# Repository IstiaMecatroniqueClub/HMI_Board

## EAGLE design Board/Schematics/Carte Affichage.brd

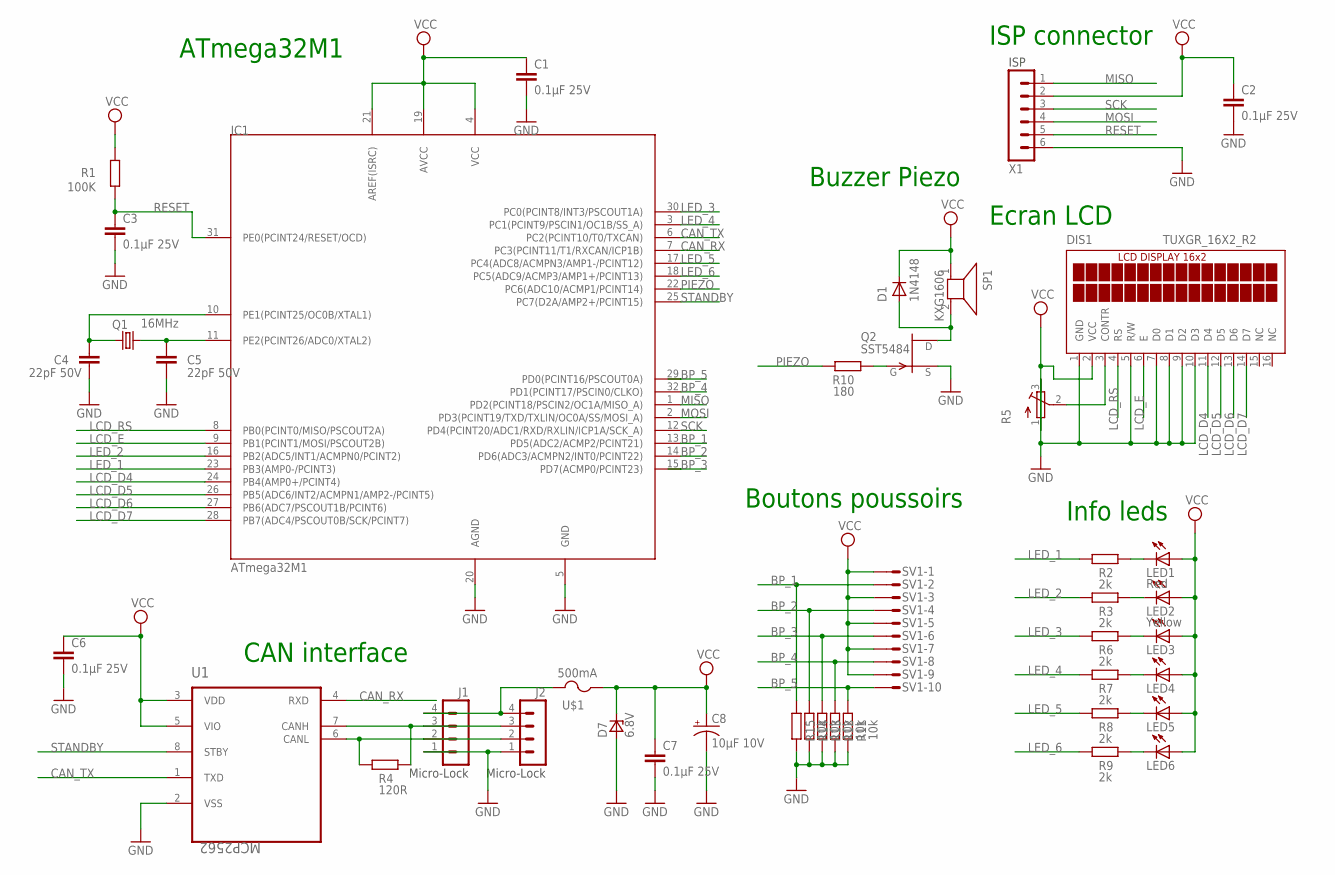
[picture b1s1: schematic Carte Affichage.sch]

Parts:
C1, C2, C3, C6, C7: 0.1µF 25V; C2012
C4, C5: 22pF 50V; C2012
C8: 10µF 10V; EIA3216
D1: 1N4148; SMA-DO214AC
D7: 6.8V; DO-214AA
DIS1: TUXGR_16X2_R2
IC1: ATmega32M1; TQFP32
J1, J2: Micro-Lock; 504195-0470
LED1: Red; VLD
LED2: Yellow; VLD
LED3, LED4, LED5, LED6: LED5MM
Q1: 16MHz; SMD_KX7
Q2: SST5484; SOT23
R1: 100K; R2012
R2, R3, R6, R7, R8, R9: 2k; R2012
R4: 120R; R2012
R5: R-TRIMM3299W; RTRIM3299W
R10: 180; R2012
R11, R12, R13, R14, R15: 10k; R2012
SP1: KXG1606; AL23P
SV1: S10P; S10P2
U1: MCP2562; SOIC8
U$1: 500mA; EIARS-481-2
X1: ISP; MINITEK_127_6WAY_SMD

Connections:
BP_1: IC1.13 (PD5(ADC2/ACMP2/PCINT21)), R15.2, SV1.P$2
BP_2: IC1.14 (PD6(ADC3/ACMPN2/INT0/PCINT22)), R14.2, SV1.P$4
BP_3: IC1.15 (PD7(ACMP0/PCINT23)), R13.2, SV1.P$6
BP_4: IC1.32 (PD1(PCINT17/PSCIN0/CLKO)), R12.2, SV1.P$8
BP_5: IC1.29 (PD0(PCINT16/PSCOUT0A)), R11.2, SV1.P$10
CAN_RX: IC1.7 (PC3(PCINT11/T1/RXCAN/ICP1B)), U1.4 (RXD)
CAN_TX: IC1.6 (PC2(PCINT10/T0/TXCAN)), U1.1 (TXD)
GND: C1.2, C2.2, C3.2, C4.2, C5.2, C6.2, C7.2, C8.C (-), D7.A, DIS1.1 (GND), DIS1.5 (R/W), DIS1.7 (D0), DIS1.8 (D1), DIS1.9 (D2), DIS1.10 (D3), IC1.5 (GND), IC1.20 (AGND), J1.1, J2.1, Q2.2 (S), R5.3 (A), R11.1, R12.1, R13.1, R14.1, R15.1, U1.2 (VSS), X1.6
LCD_D4: DIS1.11 (D4), IC1.24 (PB4(AMP0+/PCINT4))
LCD_D5: DIS1.12 (D5), IC1.26 (PB5(ADC6/INT2/ACMPN1/AMP2-/PCINT5))
LCD_D6: DIS1.13 (D6), IC1.27 (PB6(ADC7/PSCOUT1B/PCINT6))
LCD_D7: DIS1.14 (D7), IC1.28 (PB7(ADC4/PSCOUT0B/SCK/PCINT7))
LCD_E: DIS1.6 (E), IC1.9 (PB1(PCINT1/MOSI/PSCOUT2B))
LCD_RS: DIS1.4 (RS), IC1.8 (PB0(PCINT0/MISO/PSCOUT2A))
LED_1: IC1.23 (PB3(AMP0-/PCINT3)), R2.2
LED_2: IC1.16 (PB2(ADC5/INT1/ACMPN0/PCINT2)), R3.2
LED_3: IC1.30 (PC0(PCINT8/INT3/PSCOUT1A)), R6.2
LED_4: IC1.3 (PC1(PCINT9/PSCIN1/OC1B/SS_A)), R7.2
LED_5: IC1.17 (PC4(ADC8/ACMPN3/AMP1-/PCINT12)), R8.2
LED_6: IC1.18 (PC5(ADC9/ACMP3/AMP1+/PCINT13)), R9.2
MISO: IC1.1 (PD2(PCINT18/PSCIN2/OC1A/MISO_A)), X1.1
MOSI: IC1.2 (PD3(PCINT19/TXD/TXLIN/OC0A/SS/MOSI_A)), X1.4
unnamed: LED3.K (C), R6.1
unnamed: LED1.C, R2.1
unnamed: LED2.C, R3.1
unnamed: J1.4, J2.4, U$1.2
unnamed: J1.2, J2.2, R4.2, U1.6 (CANL)
unnamed: J1.3, J2.3, R4.1, U1.7 (CANH)
unnamed: C5.1, IC1.11 (PE2(PCINT26/ADC0/XTAL2)), Q1.3 (2)
unnamed: LED4.K (C), R7.1
unnamed: C4.1, IC1.10 (PE1(PCINT25/OC0B/XTAL1)), Q1.1
unnamed: Q2.3 (G), R10.2
unnamed: D1.A, Q2.1 (D), SP1.2
unnamed: LED5.K (C), R8.1
unnamed: DIS1.3 (CONTR), R5.2 (S)
unnamed: LED6.K (C), R9.1
PIEZO: IC1.22 (PC6(ADC10/ACMP1/PCINT14)), R10.1
RESET: C3.1, IC1.31 (PE0(PCINT24/RESET/OCD)), R1.1, X1.5
SCK: IC1.12 (PD4(PCINT20/ADC1/RXD/RXLIN/ICP1A/SCK_A)), X1.3
STANDBY: IC1.25 (PC7(D2A/AMP2+/PCINT15)), U1.8 (STBY)
VCC: C1.1, C2.1, C6.1, C7.1, C8.A (+), D1.K (C), D7.C, DIS1.2 (VCC), IC1.4 (VCC), IC1.19 (AVCC), IC1.21 (AREF(ISRC)), LED1.A, LED2.A, LED3.A, LED4.A, LED5.A, LED6.A, R1.2, R5.1 (E), SP1.1, SV1.P$1, SV1.P$3, SV1.P$5, SV1.P$7, SV1.P$9, U1.3 (VDD), U1.5 (VIO), U$1.1, X1.2

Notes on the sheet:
ISP connector
Info leds
CAN interface
ATmega32M1
Ecran LCD
Boutons poussoirs
Buzzer Piezo

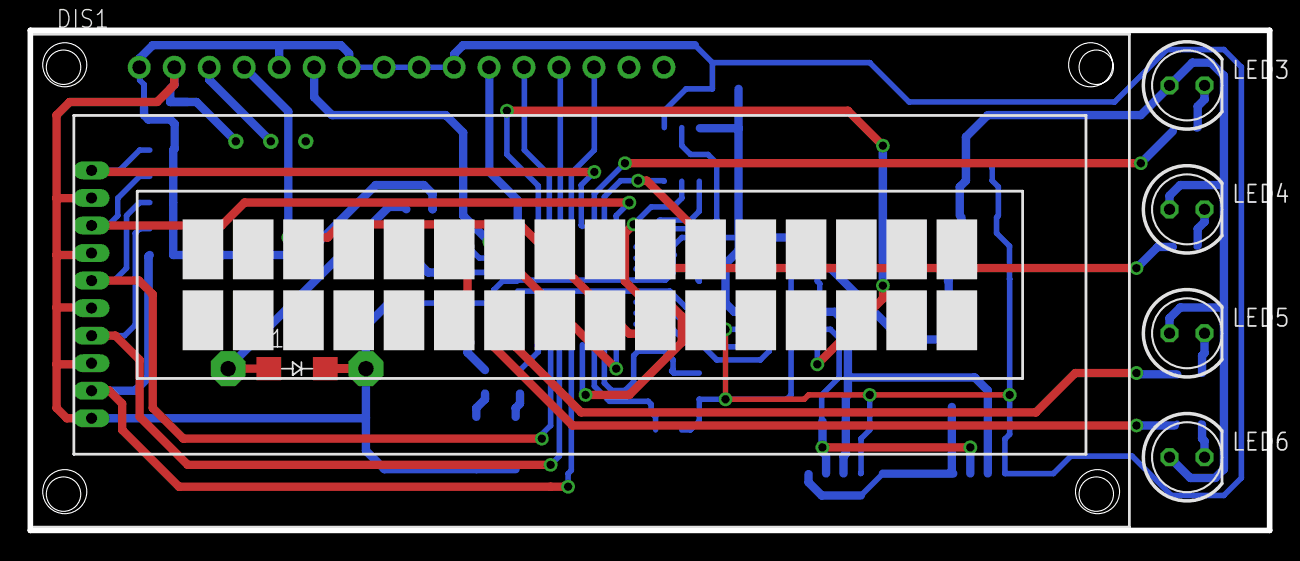
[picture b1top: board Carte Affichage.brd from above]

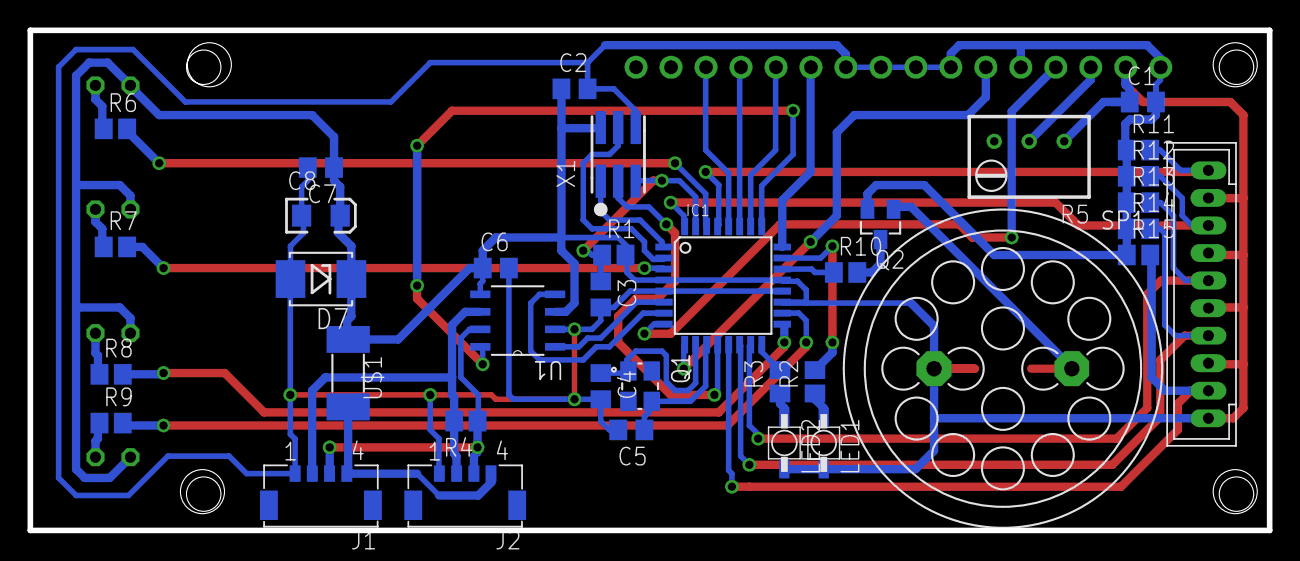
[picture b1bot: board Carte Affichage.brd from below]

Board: 2 copper layers, 90.0 x 36.3 mm, 42 parts (36 on the bottom side), 41 nets.

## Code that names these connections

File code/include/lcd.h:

//LCD Functions Developed by electroSome
#define eS_PORTB0 10
#define eS_PORTB1 11
#define eS_PORTB2 12
#define eS_PORTB3 13
#define eS_PORTB4 14
#define eS_PORTB5 15
#define eS_PORTB6 16
#define eS_PORTB7 17
#define eS_PORTC0 20
#define eS_PORTC1 21
#define eS_PORTC2 22
#define eS_PORTC3 23
#define eS_PORTC4 24
#define eS_PORTC5 25
#define eS_PORTC6 26
#define eS_PORTC7 27
#define eS_PORTD0 30
#define eS_PORTD1 31
#define eS_PORTD2 32
#define eS_PORTD3 33
#define eS_PORTD4 34
#define eS_PORTD5 35
#define eS_PORTD6 36
#define eS_PORTD7 37

#ifndef D0
#define D0 eS_PORTB0
#define D1 eS_PORTB1
#define D2 eS_PORTB2
#define D3 eS_PORTB3
#endif

#include<util/delay.h>

void pinChange(int a, int b)
{
	if(b == 0)
	{
		if(a == eS_PORTB0)
		  PORTB &= ~(1<<PB0);  
		else if(a == eS_PORTB1)
		  PORTB &= ~(1<<PB1);
		else if(a == eS_PORTB2)
		  PORTB &= ~(1<<PB2);  
		else if(a == eS_PORTB3)
		  PORTB &= ~(1<<PB3);  
		else if(a == eS_PORTB4)
		  PORTB &= ~(1<<PB4);  
		else if(a == eS_PORTB5)
		  PORTB &= ~(1<<PB5);  
		else if(a == eS_PORTB6)
		  PORTB &= ~(1<<PB6);  
		else if(a == eS_PORTB7)
		  PORTB &= ~(1<<PB7);
		else if(a == eS_PORTC0)
		  PORTC &= ~(1<<PC0);   
		else if(a == eS_PORTC1)
		  PORTC &= ~(1<<PC1); 
		else if(a == eS_PORTC2)
		  PORTC &= ~(1<<PC2);
		else if(a == eS_PORTC3)
		  PORTC &= ~(1<<PC3);   
		else if(a == eS_PORTC4)
		  PORTC &= ~(1<<PC4);  
		else if(a == eS_PORTC5)
		  PORTC &= ~(1<<PC5);  
        else if(a == eS_PORTC6)
          PORTC &= ~(1<<PC6);		
		else if(a == eS_PORTC7)
		  PORTC &= ~(1<<PC7);
		else if(a == eS_PORTD0)
		  PORTD &= ~(1<<PD0);
		else if(a == eS_PORTD1)
		  PORTD &= ~(1<<PD1);  
		else if(a == eS_PORTD2)
		  PORTD &= ~(1<<PD2);
		else if(a == eS_PORTD3)
		  PORTD &= ~(1<<PD3);
		else if(a == eS_PORTD4)
		  PORTD &= ~(1<<PD4);
		else if(a == eS_PORTD5)
		  PORTD &= ~(1<<PD5);
		else if(a == eS_PORTD6)
		  PORTD &= ~(1<<PD6);   
		else if(a == eS_PORTD7)
		  PORTD &= ~(1<<PD7);           
	}
	else
	{
		if(a == eS_PORTB0)
	  	  PORTB |= (1<<PB0);
		else if(a == eS_PORTB1)
		  PORTB |= (1<<PB1);
		else if(a == eS_PORTB2)
		  PORTB |= (1<<PB2);
		else if(a == eS_PORTB3)
		  PORTB |= (1<<PB3);
		else if(a == eS_PORTB4)
		  PORTB |= (1<<PB4);
		else if(a == eS_PORTB5)
		  PORTB |= (1<<PB5);
		else if(a == eS_PORTB6)
		  PORTB |= (1<<PB6);
		else if(a == eS_PORTB7)
		  PORTB |= (1<<PB7);
		else if(a == eS_PORTC0)
		  PORTC |= (1<<PC0);
		else if(a == eS_PORTC1)
		  PORTC |= (1<<PC1);
		else if(a == eS_PORTC2)
	  	  PORTC |= (1<<PC2);
		else if(a == eS_PORTC3)
		  PORTC |= (1<<PC3);
		else if(a == eS_PORTC4)
		  PORTC |= (1<<PC4);
		else if(a == eS_PORTC5)
		  PORTC |= (1<<PC5);
		else if(a == eS_PORTC6)
		  PORTC |= (1<<PC6);  
		else if(a == eS_PORTC7)
		  PORTC |= (1<<PC7);
		else if(a == eS_PORTD0)
		  PORTD |= (1<<PD0);
		else if(a == eS_PORTD1)
		  PORTD |= (1<<PD1);
		else if(a == eS_PORTD2)
		  PORTD |= (1<<PD2);
		else if(a == eS_PORTD3)
		  PORTD |= (1<<PD3);
		else if(a == eS_PORTD4)
		  PORTD |= (1<<PD4);
		else if(a == eS_PORTD5)
		  PORTD |= (1<<PD5);
		else if(a == eS_PORTD6)
		  PORTD |= (1<<PD6);
		else if(a == eS_PORTD7)
		  PORTD |= (1<<PD7);
	}
}



//LCD 8 Bit Interfacing Functions
void Lcd8_Port(char a)
{
	if(a & 1)
	pinChange(D0,1);
	else
	pinChange(D0,0);
	
	if(a & 2)
	pinChange(D1,1);
	else
	pinChange(D1,0);
	
	if(a & 4)
	pinChange(D2,1);
	else
	pinChange(D2,0);
	
	if(a & 8)
	pinChange(D3,1);
	else
	pinChange(D3,0);
	
	if(a & 16)
	pinChange(D4,1);
	else
	pinChange(D4,0);

	if(a & 32)
	pinChange(D5,1);
	else
	pinChange(D5,0);
	
	if(a & 64)
	pinChange(D6,1);
	else
	pinChange(D6,0);
	
	if(a & 128)
	pinChange(D7,1);
	else
	pinChange(D7,0);
}
void Lcd8_Cmd(char a)
{
	pinChange(RS,0);             // => RS = 0
	Lcd8_Port(a);             //Data transfer
	pinChange(EN,1);             // => E = 1
	_delay_ms(1);
	pinChange(EN,0);             // => E = 0
	_delay_ms(1);
}

void Lcd8_Clear()
{
	Lcd8_Cmd(1);
}

void Lcd8_Set_Cursor(char a, char b)
{
	if(a == 1)
	Lcd8_Cmd(0x80 + b);
	else if(a == 2)
	Lcd8_Cmd(0xC0 + b);
}

void Lcd8_Init()
{
	pinChange(RS,0);
	pinChange(EN,0);
	_delay_ms(20);
	///////////// Reset process from datasheet /////////
	Lcd8_Cmd(0x30);
	_delay_ms(5);
	Lcd8_Cmd(0x30);
	_delay_ms(1);
	Lcd8_Cmd(0x30);
	_delay_ms(10);
	/////////////////////////////////////////////////////
	Lcd8_Cmd(0x38);    //function set
	Lcd8_Cmd(0x0C);    //display on,cursor off,blink off
	Lcd8_Cmd(0x01);    //clear display
	Lcd8_Cmd(0x06);    //entry mode, set increment
}

void Lcd8_Write_Char(char a)
{
	pinChange(RS,1);             // => RS = 1
	Lcd8_Port(a);             //Data transfer
	pinChange(EN,1);             // => E = 1
	_delay_ms(1);
	pinChange(EN,0);             // => E = 04
	_delay_ms(1);
}

void Lcd8_Write_String(char *a)
{
	int i;
	for(i=0;a[i]!='\0';i++)
	Lcd8_Write_Char(a[i]);
}

void Lcd8_Shift_Right()
{
	Lcd8_Cmd(0x1C);
}

void Lcd8_Shift_Left()
{
	Lcd8_Cmd(0x18);
}
//End LCD 8 Bit Interfacing Functions

//LCD 4 Bit Interfacing Functions

void Lcd4_Port(char a)
{
	if(a & 1)
	pinChange(D4,1);
	else
	pinChange(D4,0);
	
	if(a & 2)
	pinChange(D5,1);
	else
	pinChange(D5,0);
	
	if(a & 4)
	pinChange(D6,1);
	else
	pinChange(D6,0);
	
	if(a & 8)
	pinChange(D7,1);
	else
	pinChange(D7,0);
}
void Lcd4_Cmd(char a)
{
	pinChange(RS,0);             // => RS = 0
	Lcd4_Port(a);
	pinChange(EN,1);            // => E = 1
	_delay_ms(1);
	pinChange(EN,0);             // => E = 0
	_delay_ms(1);
}

void Lcd4_Clear()
{
	Lcd4_Cmd(0);
	Lcd4_Cmd(1);
}

void Lcd4_Set_Cursor(char a, char b)
{
	char temp,z,y;
	if(a == 1)
	{
		temp = 0x80 + b;
		z = temp>>4;
		y = (0x80+b) & 0x0F;
		Lcd4_Cmd(z);
		Lcd4_Cmd(y);
	}
	else if(a == 2)
	{
		temp = 0xC0 + b;
		z = temp>>4;
		y = (0xC0+b) & 0x0F;
		Lcd4_Cmd(z);
		Lcd4_Cmd(y);
	}
}

void Lcd4_Init()
{
	Lcd4_Port(0x00);
	_delay_ms(20);
	///////////// Reset process from datasheet /////////
	Lcd4_Cmd(0x03);
	_delay_ms(5);
	Lcd4_Cmd(0x03);
	_delay_ms(11);
	Lcd4_Cmd(0x03);
	/////////////////////////////////////////////////////
	Lcd4_Cmd(0x02);
	Lcd4_Cmd(0x02);
	Lcd4_Cmd(0x08);
	Lcd4_Cmd(0x00);
	Lcd4_Cmd(0x0C);
	Lcd4_Cmd(0x00);
	Lcd4_Cmd(0x06);
}

void Lcd4_Write_Char(char a)
{
	char temp,y;
	temp = a&0x0F;
	y = a&0xF0;
	pinChange(RS,1);             // => RS = 1
	Lcd4_Port(y>>4);             //Data transfer
	pinChange(EN,1);
	_delay_ms(1);
	pinChange(EN,0);
	_delay_ms(1);
	Lcd4_Port(temp);
	pinChange(EN,1);
	_delay_ms(1);
	pinChange(EN,0);
	_delay_ms(1);
}

void Lcd4_Write_String(char *a)
{
	int i;
	for(i=0;a[i]!='\0';i++)
	Lcd4_Write_Char(a[i]);
}

void Lcd4_Shift_Right()
{
	Lcd4_Cmd(0x01);
	Lcd4_Cmd(0x0C);
}

void Lcd4_Shift_Left()
{
	Lcd4_Cmd(0x01);
	Lcd4_Cmd(0x08);
}
//End LCD 4 Bit Interfacing Functions

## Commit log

2017-06-16 adding source code and documentation
2017-09-20 Initial deposit
